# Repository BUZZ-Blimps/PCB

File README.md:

# DEPRECATED
Please do not use or merge this branch. It will break everything.

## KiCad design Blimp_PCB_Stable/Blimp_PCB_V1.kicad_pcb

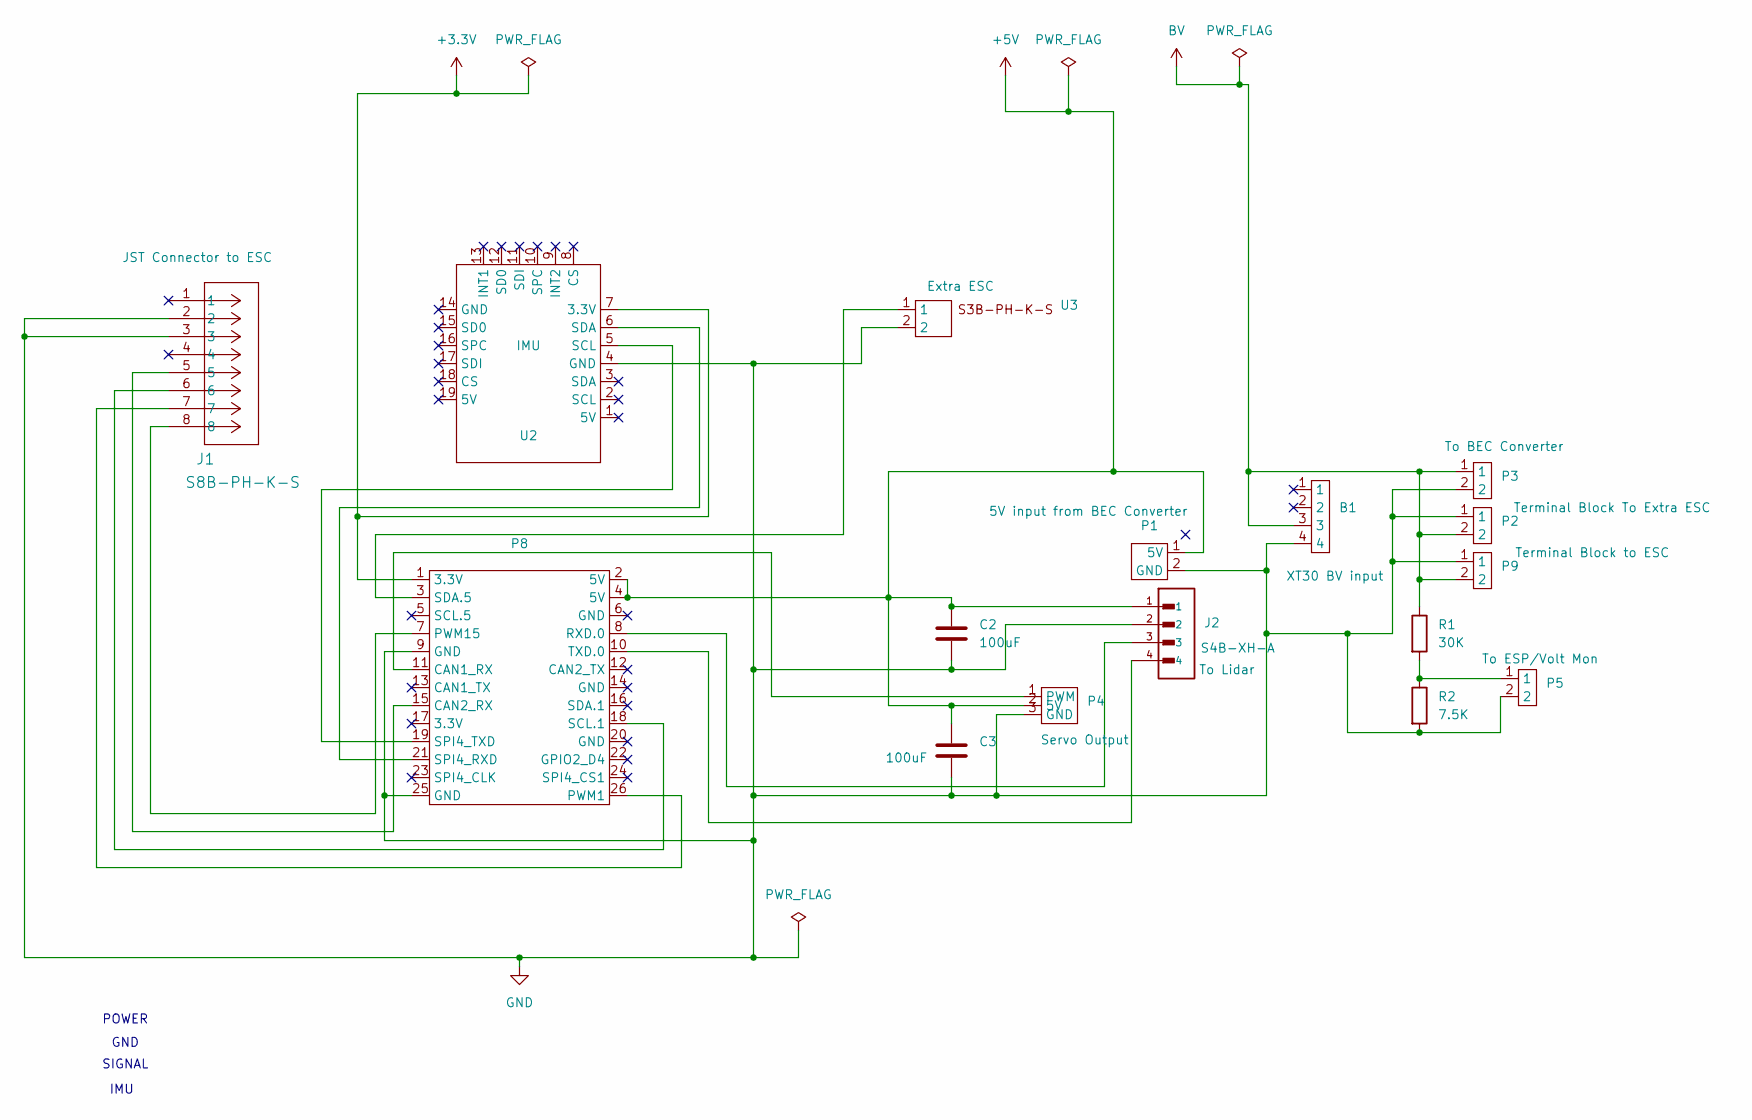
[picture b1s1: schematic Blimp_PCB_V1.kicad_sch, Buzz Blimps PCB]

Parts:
B1: XT30
C2, C3: 100uF; C_0603_1608Metric_Pad1.08x0.95mm_HandSolder
J1: S8B-PH-K-S; JST_SH_BM08B-SRSS-TB_1x08-1MP_P1.00mm_Vertical
J2: S4B-XH-A; JST_S4B-XH-A
P1, P3: JST_XH_B2B-XH-A_1x02_P2.50mm_Vertical
P2, P9: TerminalBlock_Phoenix_MKDS-1,5-2_1x02_P5.00mm_Horizontal
P4: PWM
P5: Shorting Pins
P8: Orange_Pi_5B
R1: 30K; C_0603_1608Metric_Pad1.08x0.95mm_HandSolder
R2: 7.5K; C_0603_1608Metric_Pad1.08x0.95mm_HandSolder
U2: Berry_IMU
U3: JST_XH_S2B-XH-A_1x02_P2.50mm_Horizontal

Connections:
+3.3V: P8.1 (3.3V), U2.7 (3.3V)
+5V: C2.1, C3.1, J2.1, P1.1 (5V), P4.2 (5V), P8.2 (5V), P8.4 (5V)
BV: B1.3, P2.2, P3.1, P9.2, R1.1
GND: B1.4, C2.2, C3.2, J1.2, J1.3, J2.2, P1.2 (GND), P2.1, P3.2, P4.3 (GND), P5.2, P8.9 (GND), P8.25 (GND), P9.1, R2.2, U2.4 (GND), U3.2
unnamed: P4.1 (PWM), P8.11 (CAN1_RX)
unnamed: P5.1, R1.2, R2.1
unnamed: J1.5, P8.15 (CAN2_RX)
unnamed: J1.7, P8.26 (PWM1)
unnamed: J1.8, P8.7 (PWM15)
unnamed: J2.3, P8.8 (RXD.0)
unnamed: J1.6, P8.18 (SCL.1)
unnamed: P8.3 (SDA.5), U3.1
unnamed: P8.21 (SPI4_RXD), U2.6 (SDA)
unnamed: P8.19 (SPI4_TXD), U2.5 (SCL)
unnamed: J2.4, P8.10 (TXD.0)

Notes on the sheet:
IMU
GND
SIGNAL
POWER

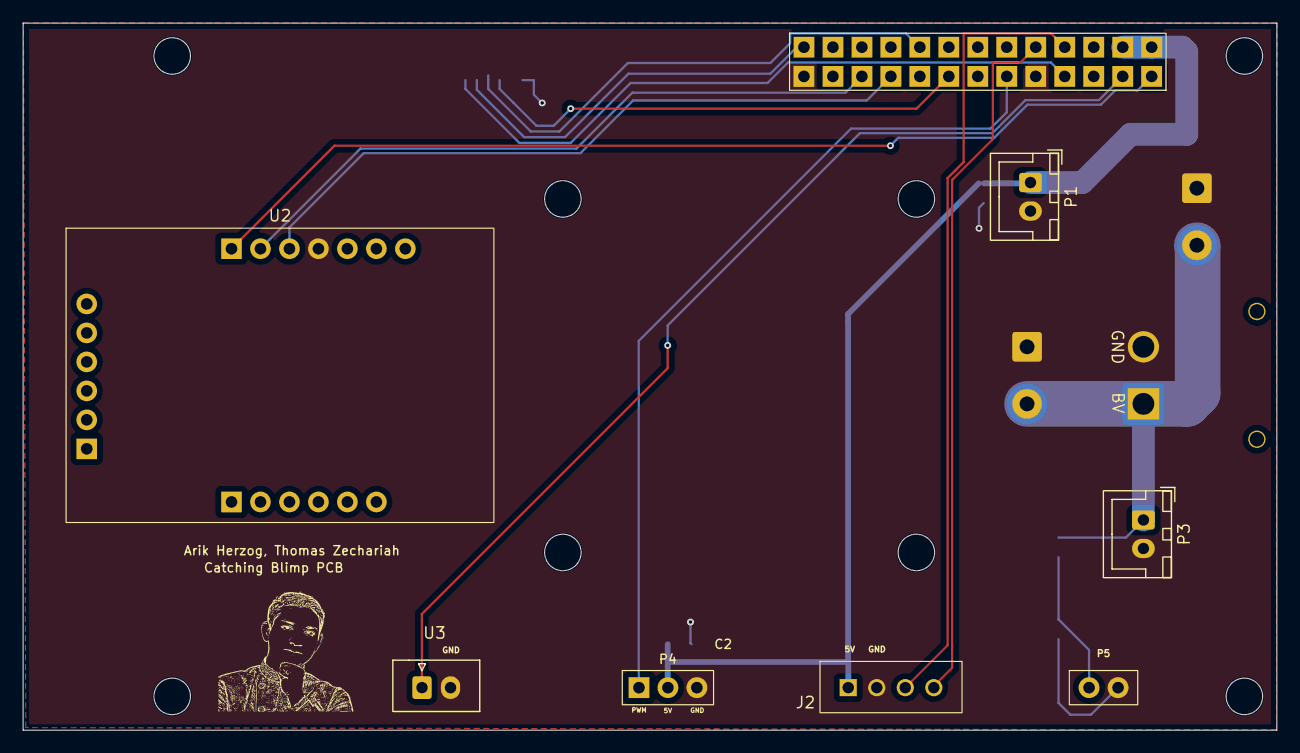
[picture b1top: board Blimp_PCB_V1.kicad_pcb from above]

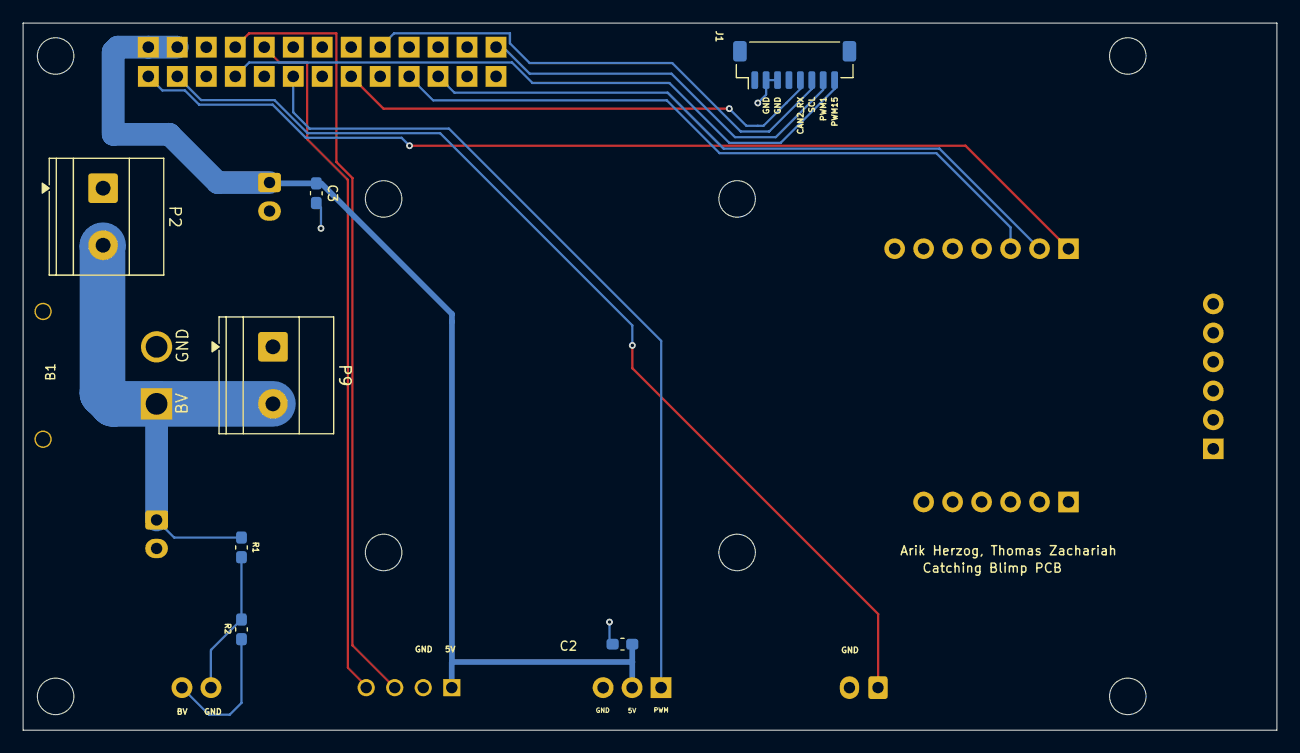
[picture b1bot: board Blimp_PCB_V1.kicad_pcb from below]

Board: 2 copper layers, 109.9 x 62.0 mm, 16 parts (8 on the bottom side), 15 nets.

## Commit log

2025-09-19 PCB Files
2026-02-13 PCBv1
2026-02-14 PCBv1.2
2026-02-14 PCBv1 modified schematic
2026-02-25 Updated JST 8pin footprint and connections
2026-02-25 Switched JST connector to SMT footprint
2026-02-25 Added proper JST Connector for Lidar, Footprint and Symbol
2026-02-25 Tiny wiring fix
2026-03-03 Flipped lidar connection and connected 5V, confused why not connected before
2026-03-13 all in one folder
2026-03-13 udpate
2026-03-13 flip connector
2026-03-14 flip again
2026-03-31 Cleaned some PCB silkscreen labels and fixed footprints for JST connectors
2026-03-31 Relabel, Fix 3D models, starting to remap not done yet
2026-04-01 Added more 3D models and cleaned up labelling
2026-04-01 fixed XT30 3D model
2026-04-01 capcaitor value fix
2026-04-01 added Berry IMU 3D model
2026-04-01 Small change in dimensions of IMU footprint
2026-04-01 Properly adjusted IMU footprint spacing and measurements by measuring CAD in fusion, removed extra 20th pin
2026-04-03 Fixed orientations, added in traces, fixed everything its perfect
2026-04-07 Added ground plane and connected everything up to it, might need to review trace sizes, connected JST 8pin to ESC signals, connected 3.3V from orangepi to IMU
2026-04-07 fixed unnecessary vias, streamlined traces
2026-04-07 quick fix
2026-04-07 Arik semi-final update
2026-04-07 Merged Arik stable update into main
2026-04-10 Arik stable update
2026-04-10 Fixed all the problems
2026-04-14 fixed DRC and footprint library erros
